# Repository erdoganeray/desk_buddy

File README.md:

# Desk Buddy Clone

ESP32-S3 tabanlı, ekranlı/sensörlü masaüstü "desk buddy" tarzı cihaz için PCB tasarım projesi.

## Konsept

İki fikrin birleşimi:

1. **Desk Buddy** — bilindik bir ürün kategorisi, ama buradaki hedef ona "canlı" bir hissiyat katmak. Bu yüzden tek bir sensör değil bir yığın var: ToF (yakınlık farkındalığı), TTP223 x2 (dokunma/okşama), MPU6050 (hareket/sallama algısı), LDR (ortam ışığına tepki), AHT20+BMP280 (çevre farkındalığı). Her biri cihazın "canlı" davranmasına küçük bir katkı.
2. **Mini oyun konsolu** — ekran (ILI9341), ses (MAX98357A), RGB LED'ler zaten bir oyun deneyimi için yeterli donanımı sağlıyor. Buna ek olarak, kartın dışarıya verdiği **ikinci (izole) I2C hattındaki 2 konnektöre**, ayrıca tasarlanacak mini I2C gamepad'ler takılabilecek — tek kişi kendi kendine, ya da iki kişi karşılıklı oynayabilecek.

Donanımsal ve yazılımsal olarak sınırları zorlayan, deneysel bir proje — revizyonlarla senaryonun çok değişmesi bekleniyor.

**Not (gamepad tasarımı için, bu PCB'yi etkilemiyor):** İki gamepad konnektörü de aynı I2C1 bus'ında paralel. Eğer iki gamepad birbirinin aynıysa (aynı sabit I2C adresi), aynı anda takıldıklarında adres çakışması olur. Gamepad kartlarında bir adres-seçim pini/jumper'ı olmalı.

## Arka plan

Bu tasarım daha önce bir kez tamamlanmış, komponentler/entegreler satın alınmıştı ancak şematik/PCB dosyaları bir bilgisayar resetinde kayboldu. Bu proje, elimizdeki satın alınmış parçalara göre tasarımı sıfırdan (KiCad'de) yeniden yapmak için açıldı.

## Cihazın planlanan özellikleri

- **MCU:** ESP32-S3-WROOM-1-N8R2 (8MB flash / 2MB PSRAM)
- **Ekran:** 2.8" ILI9341 dokunmatik LCD (XPT2046 touch), SPI, 240x320
- **Sensörler (I2C0, iç bus):** ToF mesafe sensörü (VL6180X), AHT20+BMP280 (sıcaklık/nem/basınç), MPU6050 (6-eksen ivme/jiroskop) — hepsi JST 2.0mm ile bağlı. Ayrıca: LDR (ortam ışığı, JST ile harici) ve TTP223 x2 (kapasitif dokunmatik, JST ile harici).
- **Genişletme (I2C1, izole harici bus):** 2x JST konnektör — gelecekte sensör veya (bkz. Konsept) mini gamepad bağlamak için.
- **LED:** Kartta 1-2 adet WS2812B RGB LED + harici olarak ~4 LED'lik seri şeride çıkış (JST 2.0mm), ikisi de ayrı GPIO'da, pil rayından besleniyor
- **Ses:** Hoparlör çıkışı, MAX98357A I2S 3W amplifikatör modülü ile sürülecek (JST ile bağlı, pil rayından beslenir)
- **Titreşim motoru:** 3V şaftsız mini motor, JST 2.0mm çıkışı, AO3400A MOSFET ile sürülecek
- **Güç:** LiPo pil + BQ24075RGTR Li-Ion şarj IC (DPPM — USB varken sistem çalışır + pil şarj olur, USB çıkınca kesintisiz pile geçer) + AP2112K-3.3 LDO
- **USB-C:** USB4110-GF-A konnektör — şarj ve programlama/seri haberleşme için
- **Butonlar:** 1x Reset, 1x Boot, 1x Power (açma/kapama — firmware deep-sleep ile). Power butonunun GPIO2'si ayrıca 3 pinli JST'ye (3V3, GND, GPIO2; J18) çıkarıldı: buton harici anahtara taşınabilir ya da GPIO2 başka bir iş için kullanılabilir
- **Genişletme:** MCU'nun kullanılmayan tek pini (GPIO48) harici pad/header'a çıkarılacak, ayrıca harici bir UART çıkışı (GPIO43/44, donanımsal varsayılan) da olacak (önceki tasarımda vardı)
- **Mekanik:** M3 vida deliği

Detaylar ve açık sorular için [schematic-notes.md](schematic-notes.md) dosyasına bakın.

## Dosya yapısı

- `README.md` — bu dosya, genel bakış
- `BOM.md` — satın alınmış komponent/entegre listesi ve notlar
- `purchase-list.md` — satın alınacak parçalar ve 0805 R/C stok kontrol listesi
- `schematic-notes.md` — şematik tasarım kararları, pin atamaları, açık sorular
- `plan.md` — geliştirme süreci / yapılacaklar listesi
- `kicad/` — KiCad proje dosyaları (KiCad üzerinden doldurulacak)
- `datasheets/` — referans alınan datasheet PDF'leri (örn. BQ24075)

## Durum

BOM netleşti, charger (BQ24075) tamamen datasheet'ten hesaplandı, ESP32-S3'ün tam GPIO ataması ve 3.3V güç bütçesi çalışıldı. **KiCad şematiği tamamlandı:** 9 sayfalık hiyerarşik şematik (`00_Power` … `08_Misc_IO`) çizildi ve tüm projede ERC temiz (0 hata, 0 uyarı).

Sıradaki aşama **PCB layout**: footprint atamaları, board outline + M3 deliği, komponent yerleşimi ve routing. `kicad/Desk Buddy.kicad_pcb` şu an boş. Güncel açık maddeler için `plan.md` ve `schematic-notes.md`'deki işaretlenmemiş kutucuklara bakın.

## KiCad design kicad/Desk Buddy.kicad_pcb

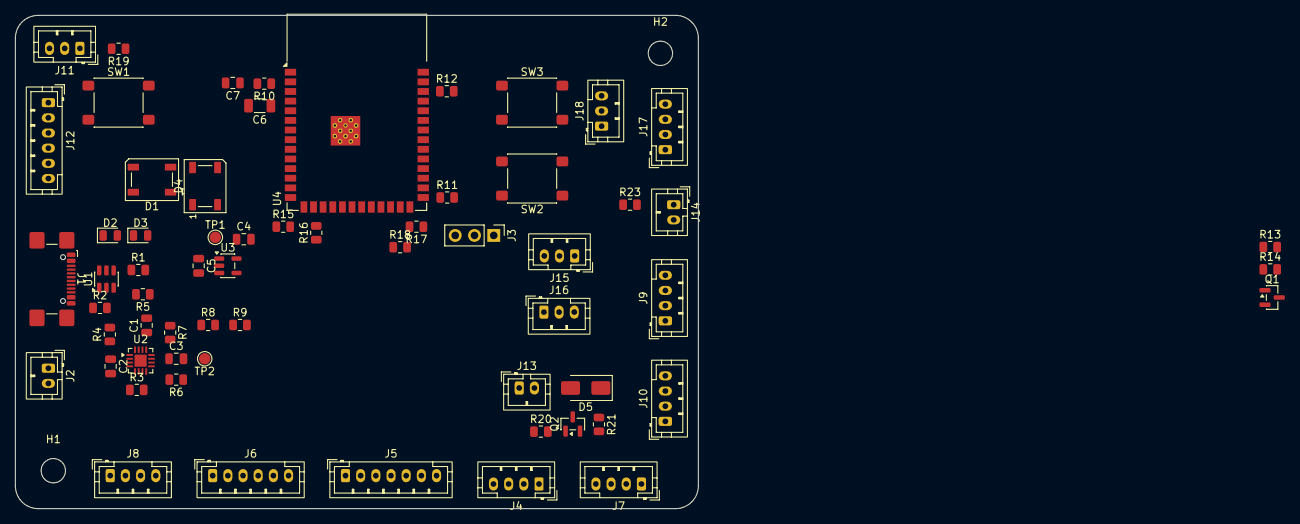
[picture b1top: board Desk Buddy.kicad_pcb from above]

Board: 2 copper layers, 90.0 x 65.0 mm, 65 parts (0 on the bottom side), 56 nets, no tracks yet.

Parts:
C1, C4, C5: 1uF; C_0805_2012Metric
C2, C3: 4.7uF; C_0805_2012Metric
C6: 47uF; C_1206_3216Metric
C7: 100nF; C_0805_2012Metric
D1, D4: WS2812B; LED_WS2812B_PLCC4_5.0x5.0mm_P3.2mm
D2: PGOOD_LED; LED_0805_2012Metric
D3: CHG_LED; LED_0805_2012Metric
D5: SS14; D_SMA
H1, H2: MountingHole_3.2mm_M3
J1: USB_C_Receptacle_USB2.0_16P; USB_C_Receptacle_GCT_USB4110
J2: LiPo; JST_PH_B2B-PH-K_1x02_P2.00mm_Vertical
J3: GPIO48; PinHeader_1x03_P2.54mm_Vertical
J4: LCD_A; JST_PH_B4B-PH-K_1x04_P2.00mm_Vertical
J5: LCD_B; JST_PH_B7B-PH-K_1x07_P2.00mm_Vertical
J6: ToF; JST_PH_B6B-PH-K_1x06_P2.00mm_Vertical
J7: AHT+BMP; JST_PH_B4B-PH-K_1x04_P2.00mm_Vertical
J8: MPU6050; JST_PH_B4B-PH-K_1x04_P2.00mm_Vertical
J9: EXP_I2C1_1; JST_PH_B4B-PH-K_1x04_P2.00mm_Vertical
J10: EXP_I2C1_2; JST_PH_B4B-PH-K_1x04_P2.00mm_Vertical
J11: EXT_LED; JST_PH_B3B-PH-K_1x03_P2.00mm_Vertical
J12: Conn_01x06; JST_PH_B6B-PH-K_1x06_P2.00mm_Vertical
J13: Motor; JST_PH_B2B-PH-K_1x02_P2.00mm_Vertical
J14: Conn_01x02; JST_PH_B2B-PH-K_1x02_P2.00mm_Vertical
J15: TTP_1; JST_PH_B3B-PH-K_1x03_P2.00mm_Vertical
J16: TTP_2; JST_PH_B3B-PH-K_1x03_P2.00mm_Vertical
J17: UART; JST_PH_B4B-PH-K_1x04_P2.00mm_Vertical
J18: PWR_BTN; JST_PH_B3B-PH-K_1x03_P2.00mm_Vertical
Q1, Q2: AO3400A; SOT-23
R1, R2: 5.1k; R_0805_2012Metric
R3, R10, R11, R12, R14, R21, R23: 10k; R_0805_2012Metric
R4, R5: 1.5k; R_0805_2012Metric
R6: 1.18k; R_0805_2012Metric
R7: 1.78k 1%; R_0805_2012Metric
R8, R9: 100k; R_0805_2012Metric
R13, R20: 100; R_0805_2012Metric
R15, R16, R17, R18: 4.7k; R_0805_2012Metric
R19: 330; R_0805_2012Metric
SW1: Push_EN; SW_SPST_PTS645Sx43SMTR92
SW2: Push_BOOT; SW_SPST_PTS645Sx43SMTR92
SW3: Switch_POWER; SW_SPST_PTS645Sx43SMTR92
TP1, TP2: TestPoint; TestPoint_Pad_D1.5mm
U1: USBLC6-2SC6; SOT-23-6
U2: BQ24075RGT; VQFN-16-1EP_3x3mm_P0.5mm_EP1.6x1.6mm
U3: AP2112K-3.3; SOT-23-5
U4: ESP32-S3-WROOM-1

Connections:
+3V3: C4.1, C6.1, J3.1, J4.1, J6.1, J7.1, J8.1, J9.1, J10.1, J15.1, J16.1, J17.1, J18.1, R10.2, R11.2, R12.2, R15.1, R16.1, R17.2, R18.2, R23.1, TP1.1 (1_1), U3.5 (VOUT), U4.2 (3V3)
/00_Power/BATT: C2.1, J2.1, R8.1, U2.2 (BAT), U2.3 (BAT)
/00_Power/USB_VBUS: C1.1, J1.A4 (VBUS), J1.A9 (VBUS), J1.B4 (VBUS), J1.B9 (VBUS), U1.5 (VBUS), U2.13 (IN)
/01_MCU/ESP32_BOOT: R11.1, SW2.1, U4.27 (IO0)
/01_MCU/ESP32_EN: C7.1, R10.1, SW1.1, U4.3 (EN)
/01_MCU/ESP32_POWER: J18.3, R12.1, SW3.1, U4.38 (IO2)
CHG_CE: U2.4 (~CE), U4.32 (IO39)
GND: C1.2, C2.2, C3.2, C4.2, C5.2, C6.2, C7.2, D1.3 (VSS), D4.3 (VSS), J1.A1 (GND), J1.A12 (GND), J1.B1 (GND), J1.B12 (GND), J1.SH (SHIELD), J2.2, J3.2, J4.2, J6.2, J7.3, J8.2, J9.2, J10.2, J11.2, J12.2, J14.2, J15.2, J16.2, J17.2, J18.2, Q1.2 (S), Q2.2 (S), R1.2, R2.2, R3.2, R6.1, R7.1, R9.2, R14.1, R21.1, SW1.2, SW2.2, SW3.2, U1.2 (GND), U2.6 (EN1), U2.8 (VSS), U2.15 (SYSOFF), U2.17 (VSS), U3.2 (GND), U4.1 (GND), U4.40 (GND), U4.41 (GND)
GPIO48_SPARE: J3.3, U4.25 (IO48)
I2C0_SCL: J6.4, J7.4, J8.4, R16.2, U4.17 (IO9)
I2C0_SDA: J6.3, J7.2, J8.3, R15.2, U4.12 (IO8)
I2C1_SCL: J9.4, J10.4, R18.1, U4.24 (IO47)
I2C1_SDA: J9.3, J10.3, R17.1, U4.35 (IO42)
I2S_BCLK: J12.3, U4.8 (IO15)
I2S_DIN: J12.5, U4.7 (IO7)
I2S_LRC: J12.4, U4.9 (IO16)
I2S_SD: J12.6, U4.28 (IO35)
LCD_BL_GATE: R13.1, U4.4 (IO4)
LCD_CS: J5.1, U4.18 (IO10)
LCD_DC: J5.2, U4.22 (IO14)
LCD_MISO: J5.5, U4.21 (IO13)
LCD_MOSI: J5.3, U4.19 (IO11)
LCD_RESET: J4.4, U4.23 (IO21)
LCD_SCK: J5.4, U4.20 (IO12)
LCD_T_CS: J5.6, U4.33 (IO40)
LCD_T_IRQ: J5.7, U4.34 (IO41)
LDR_ADC: J14.1, R23.2, U4.39 (IO1)
MOTOR_PWM: R20.1, U4.29 (IO36)
unnamed: D1.2 (DOUT), D4.4 (DIN)
unnamed: D2.1 (K), R4.2
unnamed: D3.1 (K), R5.2
unnamed: D5.2 (A), J13.2, Q2.3 (D)
unnamed: J1.A5 (CC1), R1.1
unnamed: J1.B5 (CC2), R2.1
unnamed: J1.A6 (D+), J1.B6 (D+), U1.3 (I/O2)
unnamed: J1.A7 (D-), J1.B7 (D-), U1.1 (I/O1)
unnamed: J11.3, R19.2
unnamed: Q1.1 (G), R13.2, R14.2
unnamed: Q2.1 (G), R20.2, R21.2
unnamed: R6.2, U2.12 (ILIM)
unnamed: R7.2, U2.16 (ISET)
unnamed: R3.1, U2.1 (TS)
unnamed: R5.1, U2.9 (~CHG)
unnamed: R4.1, U2.7 (~PGOOD)
TOF_INT: J6.5, U4.11 (IO18)
TOF_SHUT: J6.6, U4.10 (IO17)
TTP223_1: J15.3, U4.30 (IO37)
TTP223_2: J16.3, U4.31 (IO38)
UART_RX: J17.4, U4.36 (RXD0)
UART_TX: J17.3, U4.37 (TXD0)
USB_D+: U1.4 (I/O2), U4.14 (USB_D+)
USB_D-: U1.6 (I/O1), U4.13 (USB_D-)
VBAT_OUT: C3.1, C5.1, D1.1 (VDD), D2.2 (A), D3.2 (A), D4.1 (VDD), D5.1 (K), J4.3, J11.1, J12.1, J13.1, Q1.3 (D), TP2.1 (1_1), U2.5 (EN2), U2.10 (OUT), U2.11 (OUT), U3.1 (VIN), U3.3 (EN)
VBAT_SENSE: R8.2, R9.1, U4.15 (IO3)
WS2812_EXT: R19.1, U4.6 (IO6)
WS2812_ONBOARD: D1.4 (DIN), U4.5 (IO5)
